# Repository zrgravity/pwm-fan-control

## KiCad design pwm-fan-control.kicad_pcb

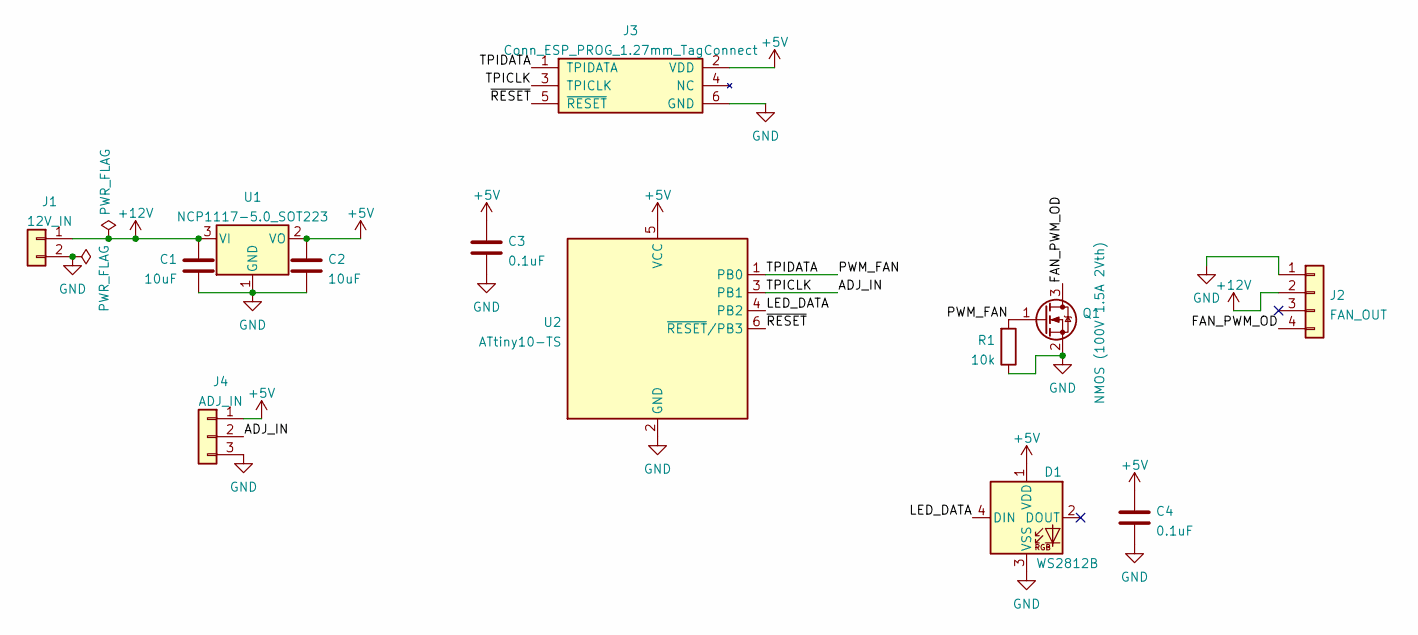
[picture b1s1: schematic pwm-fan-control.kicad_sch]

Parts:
C1, C2: 10uF; C_0805_2012Metric
C3, C4: 0.1uF; C_0603_1608Metric
D1: WS2812B; LED_WS2812B_PLCC4_5.0x5.0mm_P3.2mm
J1: 12V_IN; conn_edge_PTH_2.54mm_2x5_02
J2: FAN_OUT; conn_edge_PTH_2.54mm_2x5_04
J3: Conn_ESP_PROG_1.27mm_TagConnect; Tag-Connect_TC2030-IDC-NL_2x03_P1.27mm_Vertical
J4: ADJ_IN; conn_edge_PTH_2.54mm_2x5_03
Q1: NMOS (100V 1.5A 2Vth); SOT-89-3
R1: 10k; R_0603_1608Metric
U1: NCP1117-5.0_SOT223; SOT-223-3_TabPin2
U2: ATtiny10-TS; SOT-23-6

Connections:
+5V: C2.1, C3.1, C4.1, D1.1 (VDD), J3.2 (VDD), J4.1, U1.2 (VO), U2.5 (VCC)
+12V: C1.2, J1.1, J2.2, U1.3 (VI)
/FAN_PWM_OD: J2.4, Q1.3 (D)
/LED_DATA: D1.4 (DIN), U2.4 (PB2)
/TPICLK: J3.3 (TPICLK), J4.2, U2.3 (PB1)
/TPIDATA: J3.1 (TPIDATA), Q1.1 (G), R1.2, U2.1 (PB0)
/~RESET: J3.5 (~RESET), U2.6 (~RESET/PB3)
GND: C1.1, C2.2, C3.2, C4.2, D1.3 (VSS), J1.2, J2.1, J3.6 (GND), J4.3, Q1.2 (S), R1.1, U1.1 (GND), U2.2 (GND)

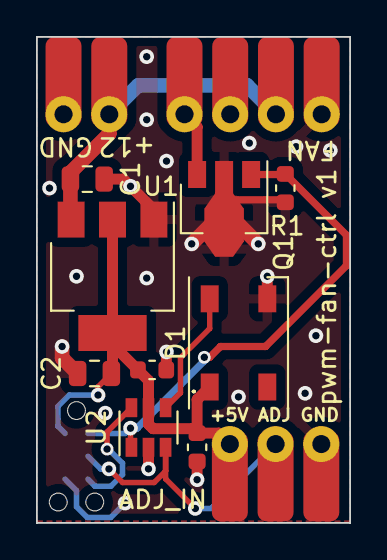
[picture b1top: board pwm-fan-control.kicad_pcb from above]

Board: 2 copper layers, 17.4 x 27.0 mm, 13 parts (1 on the bottom side), 8 nets.

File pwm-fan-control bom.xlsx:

Comment | Designator | Footprint | LCSC | Digikey | Mouser
10uF | C1,C2 | Capacitor_SMD:C_0805_2012Metric | Stock
0.1uF | C3,C4 | Capacitor_SMD:C_0603_1608Metric | Stock
WS2812B | D1 | LED_SMD:LED_WS2812B_PLCC4_5.0x5.0mm_P3.2mm | C139127
12V_IN | J1 | 0 - GIE Connectors, Terminal Blocks:conn_edge_PTH_2.54mm_2x5_02 | Wire or 0.1" male header
FAN_OUT | J2 | 0 - GIE Connectors, Terminal Blocks:conn_edge_PTH_2.54mm_2x5_04 | Wire or 0.1" male header
Conn_ESP_PROG_1.27mm_TagConnect | J3 | Connector:Tag-Connect_TC2030-IDC-NL_2x03_P1.27mm_Vertical | TagConnect - no BOM item
ADJ_IN | J4 | 0 - GIE Connectors, Terminal Blocks:conn_edge_PTH_2.54mm_2x5_03 | Wire or 0.1" male header
NMOS (100V 1.5A 2Vth) | Q1 | Package_TO_SOT_SMD:SOT-89-3 | C161844
10k | R1 | Resistor_SMD:R_0603_1608Metric | Stock
NCP1117-5.0_SOT223 | U1 | Package_TO_SOT_SMD:SOT-223-3_TabPin2 | C17314 |  | 863-NCP1117ST50T3G
ATtiny10-TS | U2 | Package_TO_SOT_SMD:SOT-23-6 | C2649376 |  | 556-ATTINY10-TS8R

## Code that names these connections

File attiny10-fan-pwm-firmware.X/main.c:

/*
 * File:   main.c
 * Author: Zeke Gustafson
 *
 * Created on October 19, 2021, 12:44 PM
 */


#include <avr/io.h>
#include <inttypes.h>
#include <util/delay.h>
#include "light_ws2812/light_ws2812_AVR/ws2812_config.h"
#include "light_ws2812/light_ws2812_AVR/Light_WS2812/light_ws2812.h"

struct cRGB led[1];

const struct cRGB color_red =   {0, 255, 0};
const struct cRGB color_green = {255, 0, 0};
const struct cRGB color_blue =  {0, 0, 255};
const struct cRGB color_white = {255, 255, 255};
const struct cRGB color_off =   {0, 0, 0};

int main(void) {
    // Setup system clock - 8MHz
    CCP = 0xD8; // Unlock registers
    CLKMSR = 0; // Internal 8MHz
    CCP = 0xD8; // Unlock registers
    CLKPSR = 0; // Prescaler set to 1
    
    // Setup Pins
    // PB0 OC0A for PWM out
    // PB1 ADC input
    DDRB &= ~(_BV(PB1));
    // PB2 Output
    DDRB |= _BV(PB2);
    // PB3 ~RESET
    
    // Setup ADC
    PRR &= ~(_BV(PRADC)); // Clear PRADC
    ADCSRA |= _BV(ADEN); // Set ADEN
    ADMUX = 1; // Set channel PB1
    DIDR0 |= _BV(ADC1D); // Set PB1 digital input disable
    ADCSRA |= (_BV(ADPS2) | _BV(ADPS1) | _BV(ADPS0)); // Set clock prescaler to 128 (8MHz/128 = 62.5kHz)
    
    // Setup Fast PWM output
    // 8MHz, Prescale = 1; TOP at 319 -> 25kHz output
    GTCCR |= _BV(TSM); // Stop timer
    ICR0 = 319;
    TCCR0B &= ~(_BV(CS02) | _BV(CS01)); // Prescale = 1; CS02 = 0, CS01 = 0; CS00 = 1
    TCCR0B |= _BV(CS00);
    // Setup OC0A - Fast PWM Mode, TOP at ICR0
    TCCR0B |= _BV(WGM03); // WGM03 = 1;
    TCCR0B |= _BV(WGM02); // WGM02 = 1;
    TCCR0A |= _BV(WGM01); // WGM01 = 1;
    TCCR0A &= ~_BV(WGM00); // WGM00 = 0;
    // Clear OC0A on match, high at BOTTOM
    TCCR0A |= _BV(COM0A1); // COM0A1 = 1;
    TCCR0A &= ~_BV(COM0A0); // COM0A0 = 0;
    // PB0 Timer OC0A Output
    DDRB |= _BV(PB0);
    
    OCR0A = 0; // Reset duty cycle to 0%
    GTCCR = 0; // Restart timer
    
    // Blink status led green 3 times
    for (uint8_t i = 0; i < 3; i++) {
        led[0] = color_green;
        ws2812_setleds(led, 1);
        _delay_ms(50);
        led[0] = color_off;
        ws2812_setleds(led, 1);
        _delay_ms(50);
    }    
    
    while (1) {
        // Read ADC
        ADCSRA |= _BV(ADSC); // Start conversion
        while (ADCSRA & _BV(ADSC)) // Wait for conversion
            ;
        uint8_t adc_result = ADCL;
        
        // Set PWM duty cycle
        // 320/255 = 64/51 
        OCR0A = (uint16_t)((uint32_t)adc_result * 64) / 51;
        
        // Set LED color by adc_result
        // 0 to 50: Green; 50 to 255 fade to yellow to red
        // Green: 0 to 127 -> 0 to 255
        // Green: 128 to 255 -> 255 to 0
        if (adc_result < 128) {
            led[0].g = adc_result * 2;
        } else {
            led[0].g = 255 - ((adc_result - 128) * 2);
        }
        // Red: 50 to 255 -> 0 to 255
        if (adc_result > 50)
            led[0].r = adc_result - 50;
        else
            led[0].r = 0;
        
        // Write to LED
        ws2812_setleds(led, 1);
    }
}

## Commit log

2021-10-19 Add KiCad gitignore
2021-10-19 Schematic layout done
2021-10-19 Component placement done
2021-10-19 Layout done
2021-10-19 Add BOM
2021-10-19 Ignore gerber files
2021-10-19 Add firmware project
2021-10-19 Plot PDF schematic
2021-10-19 Basic system setup and ADC reading
2021-10-19 Timer0 PWM setup
2021-11-02 Add interactive html BOM
2021-11-02 Fix main clock prescaler
2021-11-02 Scale ADC value
2021-11-02 Add light_ws2812 library as submodule
2021-11-02 Add light_ws2812 library to project
2021-11-03 Set led green
2021-11-03 Blink colors
2021-11-03 Add F_CPU definition
2021-11-03 Blink green 3x on powerup
2021-11-03 Add LED fade
2021-11-03 Change PWM to 25kHz
